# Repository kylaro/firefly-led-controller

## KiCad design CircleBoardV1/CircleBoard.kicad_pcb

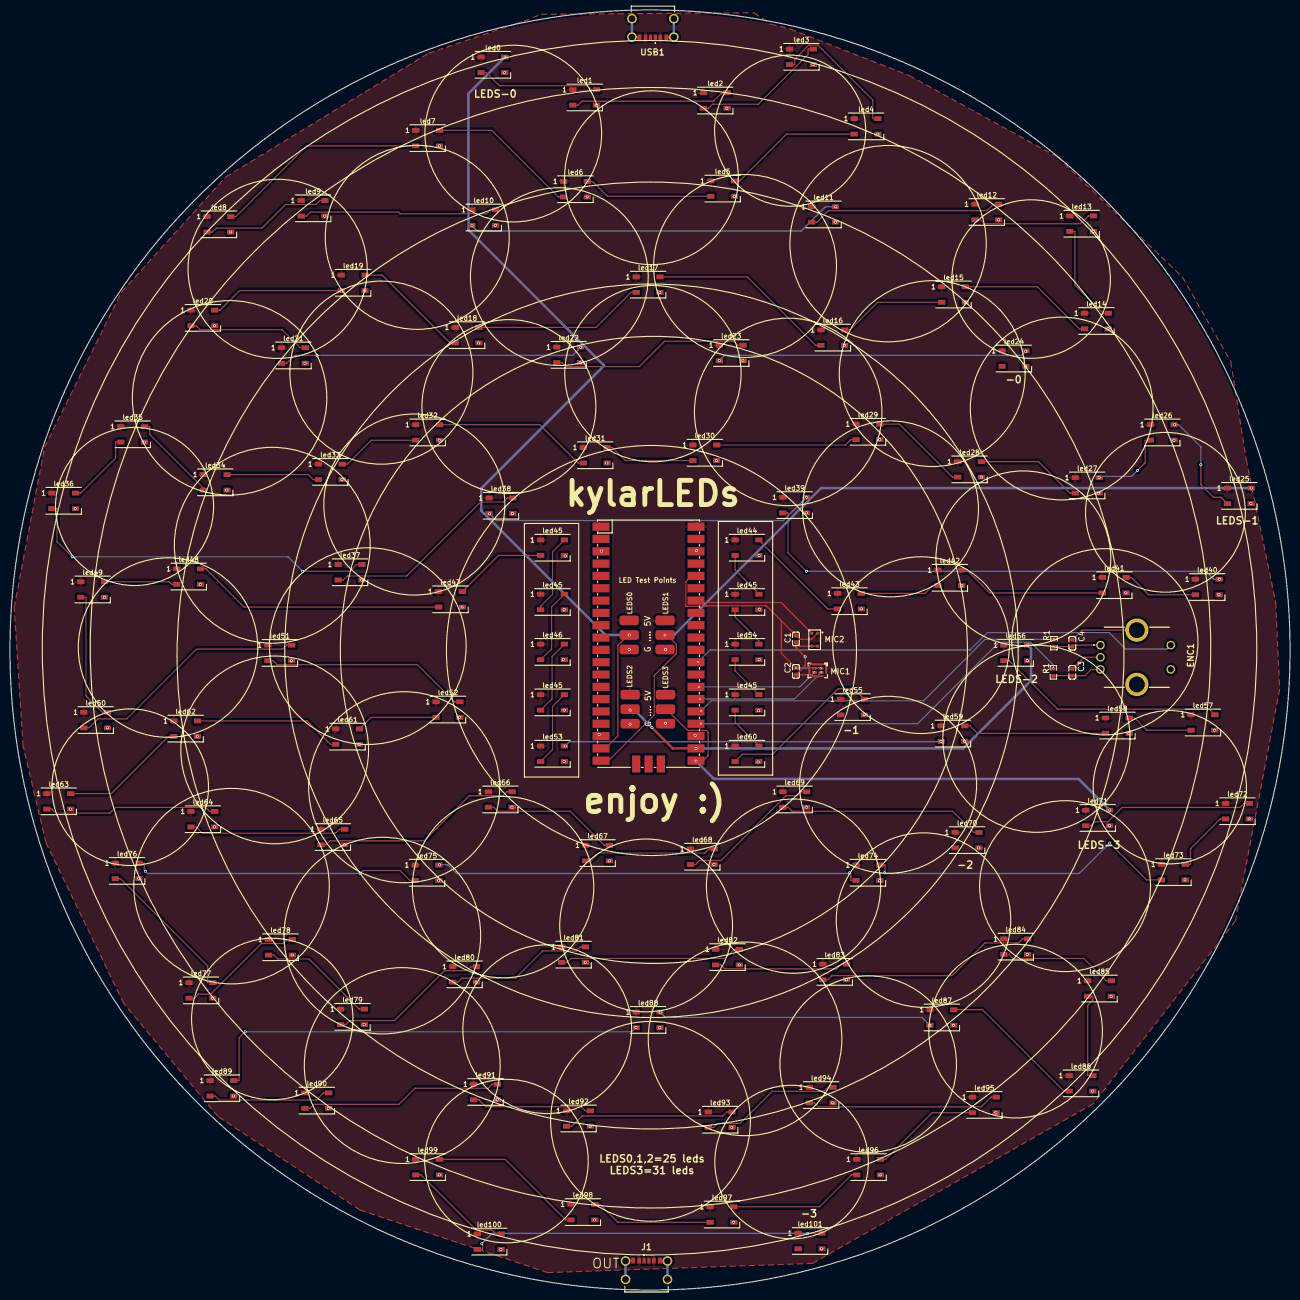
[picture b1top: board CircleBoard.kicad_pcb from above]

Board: 2 copper layers, 264.0 x 264.0 mm, 122 parts (0 on the bottom side), 117 nets.

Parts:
C1, C2, C3, C4: C0603
ENC1: PEC12R-4215F-S0024; PEC12R-4XXXF-SXXXX_court
J1: USB4125-GF-A-0190; USB4125GFA0190
LEDS0, LEDS1, LEDS2, LEDS3: ledstrip_3pin_10mm
MIC1: MIC-SMD_8P-L3.0-W4.0-P0.85-BL
MIC2: MIC-SMD_4P-L3.8-W2.3-P2.66-BR
R1, R1#2: R0603
U2: Pico; RPi_Pico_SMD_TH_removes_novia
USB1: USB4125-GF-A-0190; USB4125GFA0190
led0, led1, led2, led3, led4, led5, led6, led7, led8, led9, led10, led11, led12, led13, led14, led15, led16, led17, led18, led19, led20, led21, led22, led23, led24, led25, led26, led27, led28, led29, led30, led31, led32, led33, led34, led35, led36, led37, led38, led39, led40, led41, led42, led43, led44, led45, led45#2, led45#3, led45#4, led45#5, led46, led47, led48, led49, led50, led51, led52, led53, led54, led55, led56, led57, led58, led59, led60, led61, led62, led63, led64, led65, led66, led67, led68, led69, led70, led71, led72, led73, led74, led75, led76, led77, led78, led79, led80, led81, led82, led83, led84, led85, led86, led87, led88, led89, led90, led91, led92, led93, led94, led95, led96, led97, led98, led99, led100, led101: LED_WS2812B_PLCC4_5.0x5.0mm_P3.2mm

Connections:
3V3: C1.2, C2.2, MIC1.1, MIC2.1, U2.36
5V: J1.A9 (VBUS_1), J1.B9 (VBUS_2), LEDS0.3, LEDS1.3, LEDS2.3, LEDS3.3, U2.VBUS, USB1.A9 (VBUS_1), USB1.B9 (VBUS_2), led0.1, led1.1, led2.1, led3.1, led4.1, led5.1, led6.1, led7.1, led8.1, led9.1, led10.1, led11.1, led12.1, led13.1, led14.1, led15.1, led16.1, led17.1, led18.1, led19.1, led20.1, led21.1, led22.1, led23.1, led24.1, led25.1, led26.1, led27.1, led28.1, led29.1, led30.1, led31.1, led32.1, led33.1, led34.1, led35.1, led36.1, led37.1, led38.1, led39.1, led40.1, led41.1, led42.1, led43.1, led44.1, led45.1, led45#2.1, led45#3.1, led45#4.1, led45#5.1, led46.1, led47.1, led48.1, led49.1, led50.1, led51.1, led52.1, led53.1, led54.1, led55.1, led56.1, led57.1, led58.1, led59.1, led60.1, led61.1, led62.1, led63.1, led64.1, led65.1, led66.1, led67.1, led68.1, led69.1, led70.1, led71.1, led72.1, led73.1, led74.1, led75.1, led76.1, led77.1, led78.1, led79.1, led80.1, led81.1, led82.1, led83.1, led84.1, led85.1, led86.1, led87.1, led88.1, led89.1, led90.1, led91.1, led92.1, led93.1, led94.1, led95.1, led96.1, led97.1, led98.1, led99.1, led100.1, led101.1
ADC2: MIC2.4, U2.34
ENC_A: R1.2, U2.GP18
ENC_A_raw: C3.1, ENC1.2, R1.1
ENC_B: R1#2.2, U2.GP19
ENC_B_raw: C4.1, ENC1.1, R1#2.1
ENC_SW: ENC1.4, U2.29
GND: C1.1, C2.1, C3.2, C4.2, ENC1.3, ENC1.5, ENC1.6, ENC1.7, J1.A12 (GND_1), J1.B12 (GND_2), J1.MH1, J1.MH2, J1.MH3, J1.MH4, LEDS0.1, LEDS1.1, LEDS2.1, LEDS3.1, MIC1.5, MIC1.6, MIC1.7, MIC1.8, MIC2.2, MIC2.3, U2.18, U2.GND, USB1.A12 (GND_1), USB1.B12 (GND_2), USB1.MH1, USB1.MH2, USB1.MH3, USB1.MH4, led0.3, led1.3, led2.3, led3.3, led4.3, led5.3, led6.3, led7.3, led8.3, led9.3, led10.3, led11.3, led12.3, led13.3, led14.3, led15.3, led16.3, led17.3, led18.3, led19.3, led20.3, led21.3, led22.3, led23.3, led24.3, led25.3, led26.3, led27.3, led28.3, led29.3, led30.3, led31.3, led32.3, led33.3, led34.3, led35.3, led36.3, led37.3, led38.3, led39.3, led40.3, led41.3, led42.3, led43.3, led44.3, led45.3, led45#2.3, led45#3.3, led45#4.3, led45#5.3, led46.3, led47.3, led48.3, led49.3, led50.3, led51.3, led52.3, led53.3, led54.3, led55.3, led56.3, led57.3, led58.3, led59.3, led60.3, led61.3, led62.3, led63.3, led64.3, led65.3, led66.3, led67.3, led68.3, led69.3, led70.3, led71.3, led72.3, led73.3, led74.3, led75.3, led76.3, led77.3, led78.3, led79.3, led80.3, led81.3, led82.3, led83.3, led84.3, led85.3, led86.3, led87.3, led88.3, led89.3, led90.3, led91.3, led92.3, led93.3, led94.3, led95.3, led96.3, led97.3, led98.3, led99.3, led100.3, led101.3
LEDS0: LEDS0.2, U2.GP14, led0.4
LEDS1: LEDS1.2, U2.GP15, led25.4
LEDS2: LEDS2.2, U2.GP17, led56.4
LEDS3: LEDS3.2, U2.GP16, led71.4
LINK01: led0.2, led1.4
LINK02: led1.2, led2.4
LINK03: led2.2, led3.4
LINK04: led3.2, led4.4
LINK05: led4.2, led5.4
LINK06: led5.2, led6.4
LINK07: led6.2, led7.4
LINK08: led7.2, led8.4
LINK09: led8.2, led9.4
LINK10: led9.2, led10.4
LINK11: led10.2, led11.4
LINK12: led11.2, led12.4
LINK13: led12.2, led13.4
LINK14: led13.2, led14.4
LINK15: led14.2, led15.4
LINK16: led15.2, led16.4
LINK17: led16.2, led17.4
LINK18: led17.2, led18.4
LINK19: led18.2, led19.4
LINK20: led19.2, led20.4
LINK21: led20.2, led21.4
LINK22: led21.2, led22.4
LINK23: led22.2, led23.4
LINK24: led23.2, led24.4
LINK26: led25.2, led26.4
LINK27: led26.2, led27.4
LINK28: led27.2, led28.4
LINK29: led28.2, led29.4
LINK30: led29.2, led30.4
LINK31: led30.2, led31.4
LINK32: led31.2, led32.4
LINK33: led32.2, led33.4
LINK34: led33.2, led34.4
LINK35: led34.2, led35.4
LINK36: led35.2, led36.4
LINK37: led36.2, led37.4
LINK38: led37.2, led38.4
LINK39: led38.2, led39.4
LINK40: led39.2, led40.4
LINK41: led40.2, led41.4
LINK42: led41.2, led42.4
LINK43: led42.2, led43.4
LINK44: led43.2, led44.4
LINK47: led45#2.2, led47.4
LINK48: led47.2, led48.4
LINK49: led48.2, led49.4
LINK50: led49.2, led50.4
LINK51: led50.2, led51.4
LINK52: led51.2, led52.4
LINK57: led56.2, led57.4
LINK58: led57.2, led58.4
LINK59: led58.2, led59.4
LINK61: led52.2, led61.4
LINK62: led61.2, led62.4
LINK63: led62.2, led63.4
LINK64: led63.2, led64.4
LINK65: led64.2, led65.4
LINK66: led65.2, led66.4
LINK67: led66.2, led67.4
LINK68: led67.2, led68.4
LINK69: led68.2, led69.4
LINK70: led69.2, led70.4
LINK72: led71.2, led72.4
LINK73: led72.2, led73.4
LINK74: led73.2, led74.4
LINK75: led74.2, led75.4
LINK76: led75.2, led76.4
LINK77: led76.2, led77.4
LINK78: led77.2, led78.4
LINK79: led78.2, led79.4
LINK80: led79.2, led80.4
LINK81: led80.2, led81.4
LINK82: led81.2, led82.4
LINK83: led82.2, led83.4
LINK84: led83.2, led84.4
LINK85: led84.2, led85.4
LINK86: led85.2, led86.4
LINK87: led86.2, led87.4
LINK88: led87.2, led88.4
LINK89: led88.2, led89.4
LINK90: led89.2, led90.4
LINK91: led90.2, led91.4
LINK92: led91.2, led92.4
LINK93: led92.2, led93.4
LINK94: led93.2, led94.4
LINK95: led94.2, led95.4
LINK96: led95.2, led96.4
LINK97: led96.2, led97.4
LINK98: led97.2, led98.4
LINK99: led98.2, led99.4
LINK100: led99.2, led100.4
LINK101: led100.2, led101.4
PDM_CLK: MIC1.3, U2.GP21
PDM_DATA: MIC1.4, U2.GP20
link_45_a: led44.2, led45#4.45A
link_45_b: led45.2, led45#2.4
link_46_b: led45#5.2, led46.4
link_47_b: led45.4, led46.2
link_53_a: led53.4, led59.2
link_54_a: led45#4.2, led54.4
link_54_b: led45#5.4, led53.2
link_55_a: led45#3.4, led54.2
link_60_a: led45#3.2, led60.4
link_61_a: led55.4, led60.2
